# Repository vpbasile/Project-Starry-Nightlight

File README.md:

# Project-Starry-Nightlight
A nightlight that projects an animated starry pattern on the ceiling using 3-Watt LEDs.

See https://schmincenzo.com/blog/category/electronic-projects/project-starry-night-light/ for more information.

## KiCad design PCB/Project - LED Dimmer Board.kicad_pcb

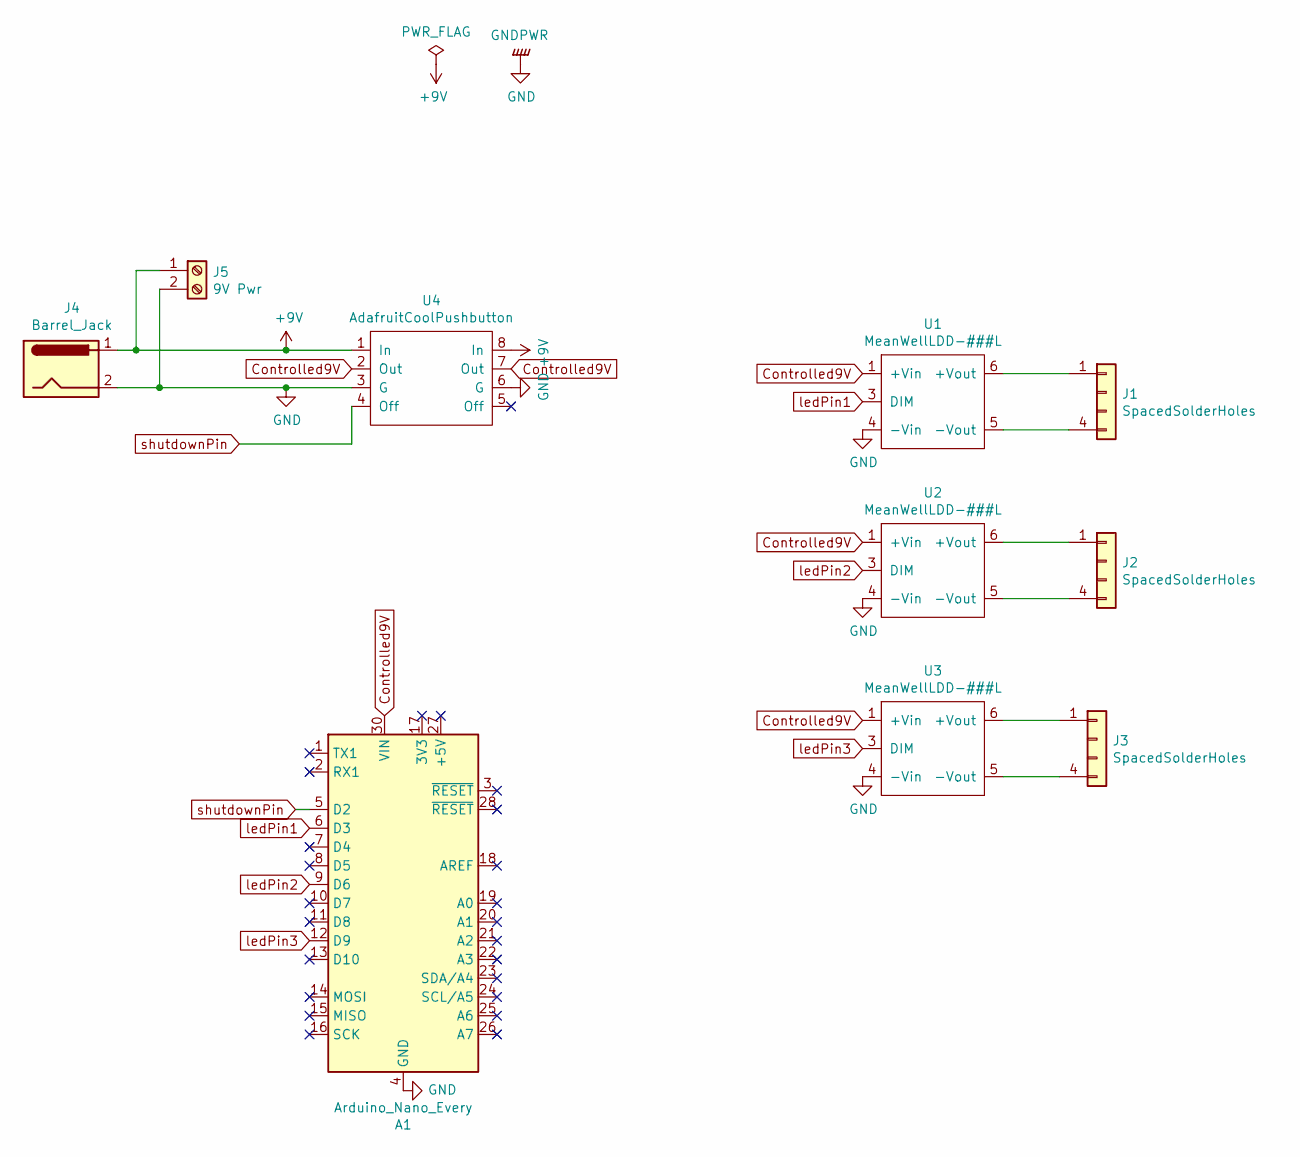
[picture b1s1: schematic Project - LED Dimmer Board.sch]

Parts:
A1: Arduino_Nano_Every; Arduino_Nano_Every_Silkscreen
J1, J2, J3: SpacedSolderHoles; TwoSpacedPins
J4: Barrel_Jack; BarrelJack_CUI_PJ-102AH_Horizontal
J5: 9V Pwr; ScrewTerminal9VLabel
U1, U2, U3: MeanWellLDD-###L; Meanwell-LDD
U4: AdafruitCoolPushbutton

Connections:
+9V: J4.1, J5.1, U4.1 (In), U4.8 (In)
Controlled9V: A1.30 (VIN), U1.1 (+Vin), U2.1 (+Vin), U3.1 (+Vin), U4.2 (Out), U4.7 (Out)
GND: A1.4 (GND), A1.29 (GND), J4.2, J5.2, U1.4 (-Vin), U2.4 (-Vin), U3.4 (-Vin), U4.3 (G), U4.6 (G)
unnamed: J1.1, U1.6 (+Vout)
unnamed: J1.4, U1.5 (-Vout)
unnamed: J2.1, U2.6 (+Vout)
unnamed: J2.4, U2.5 (-Vout)
unnamed: J3.1, U3.6 (+Vout)
unnamed: J3.4, U3.5 (-Vout)
ledPin1: A1.6 (D3), U1.3 (DIM)
ledPin2: A1.9 (D6), U2.3 (DIM)
ledPin3: A1.12 (D9), U3.3 (DIM)
shutdownPin: A1.5 (D2), U4.4 (Off)

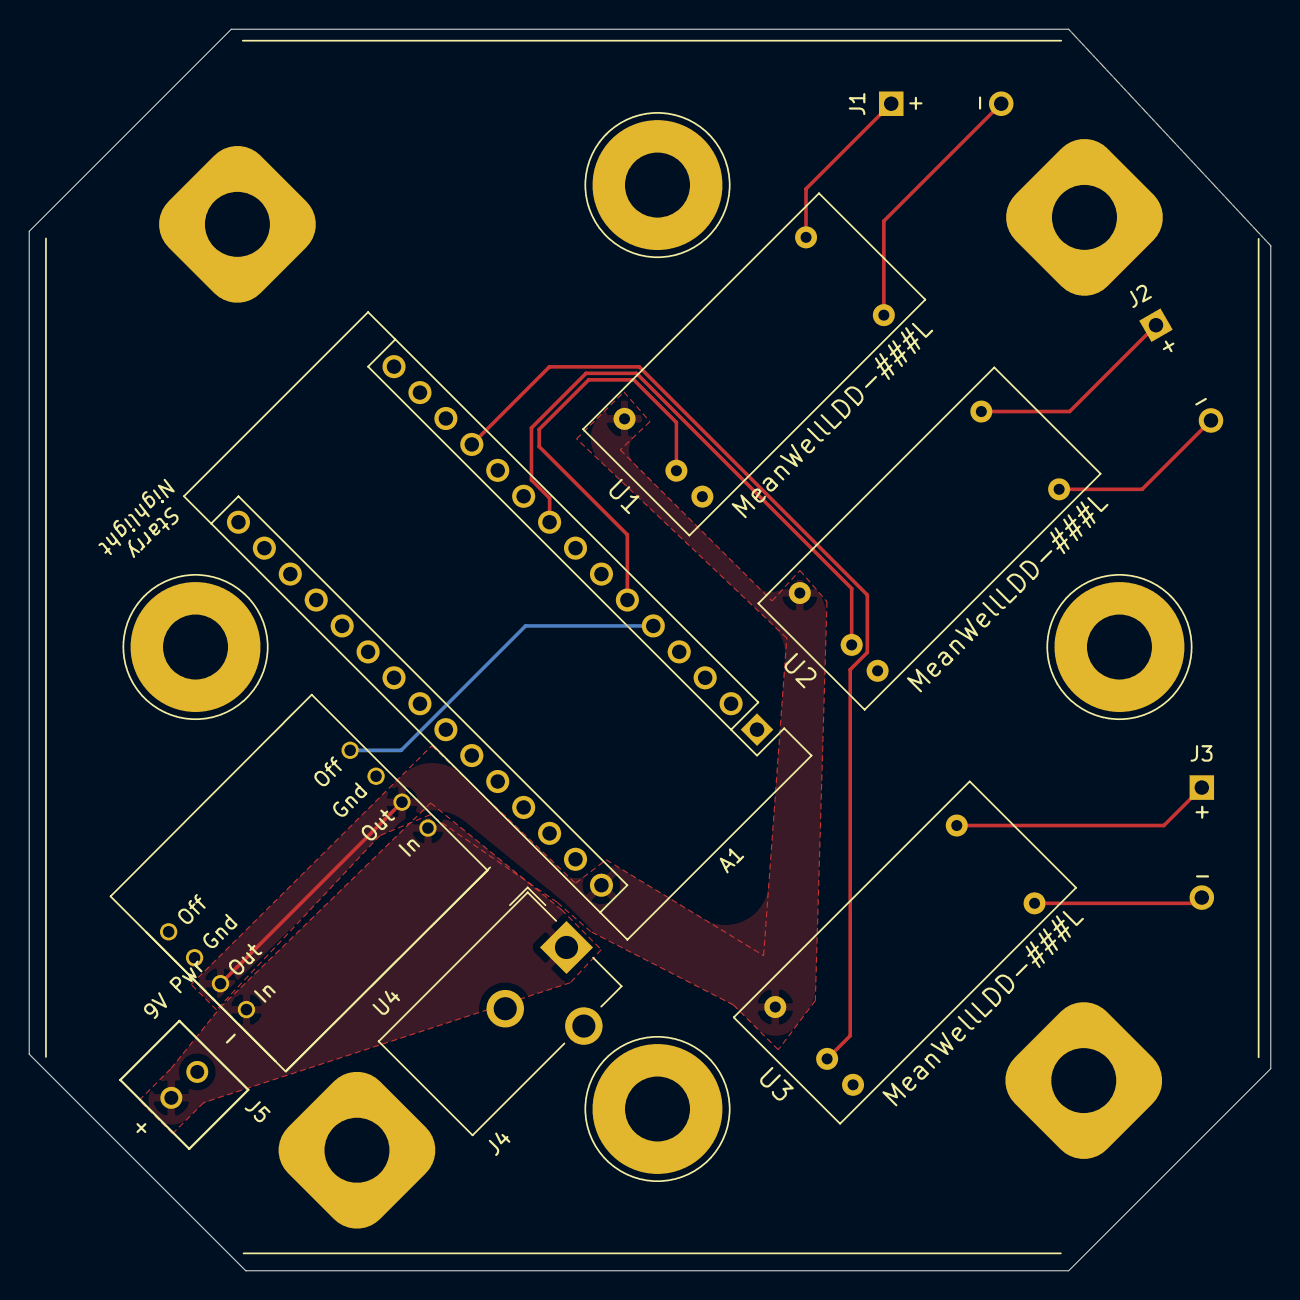
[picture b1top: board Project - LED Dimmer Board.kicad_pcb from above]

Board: 2 copper layers, 86.0 x 86.0 mm, 10 parts (0 on the bottom side), 13 nets.

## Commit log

2021-03-27 Updating Directory Structure
2021-03-28 Incorporating Nathan's improvements
2021-03-28 Adding PCB Design Files
2021-04-27 Adding laser cutting files
2021-08-26 Adding two Arduino projects
    Of note is the Continuous one, for Nick's DeepSea Nightlight
